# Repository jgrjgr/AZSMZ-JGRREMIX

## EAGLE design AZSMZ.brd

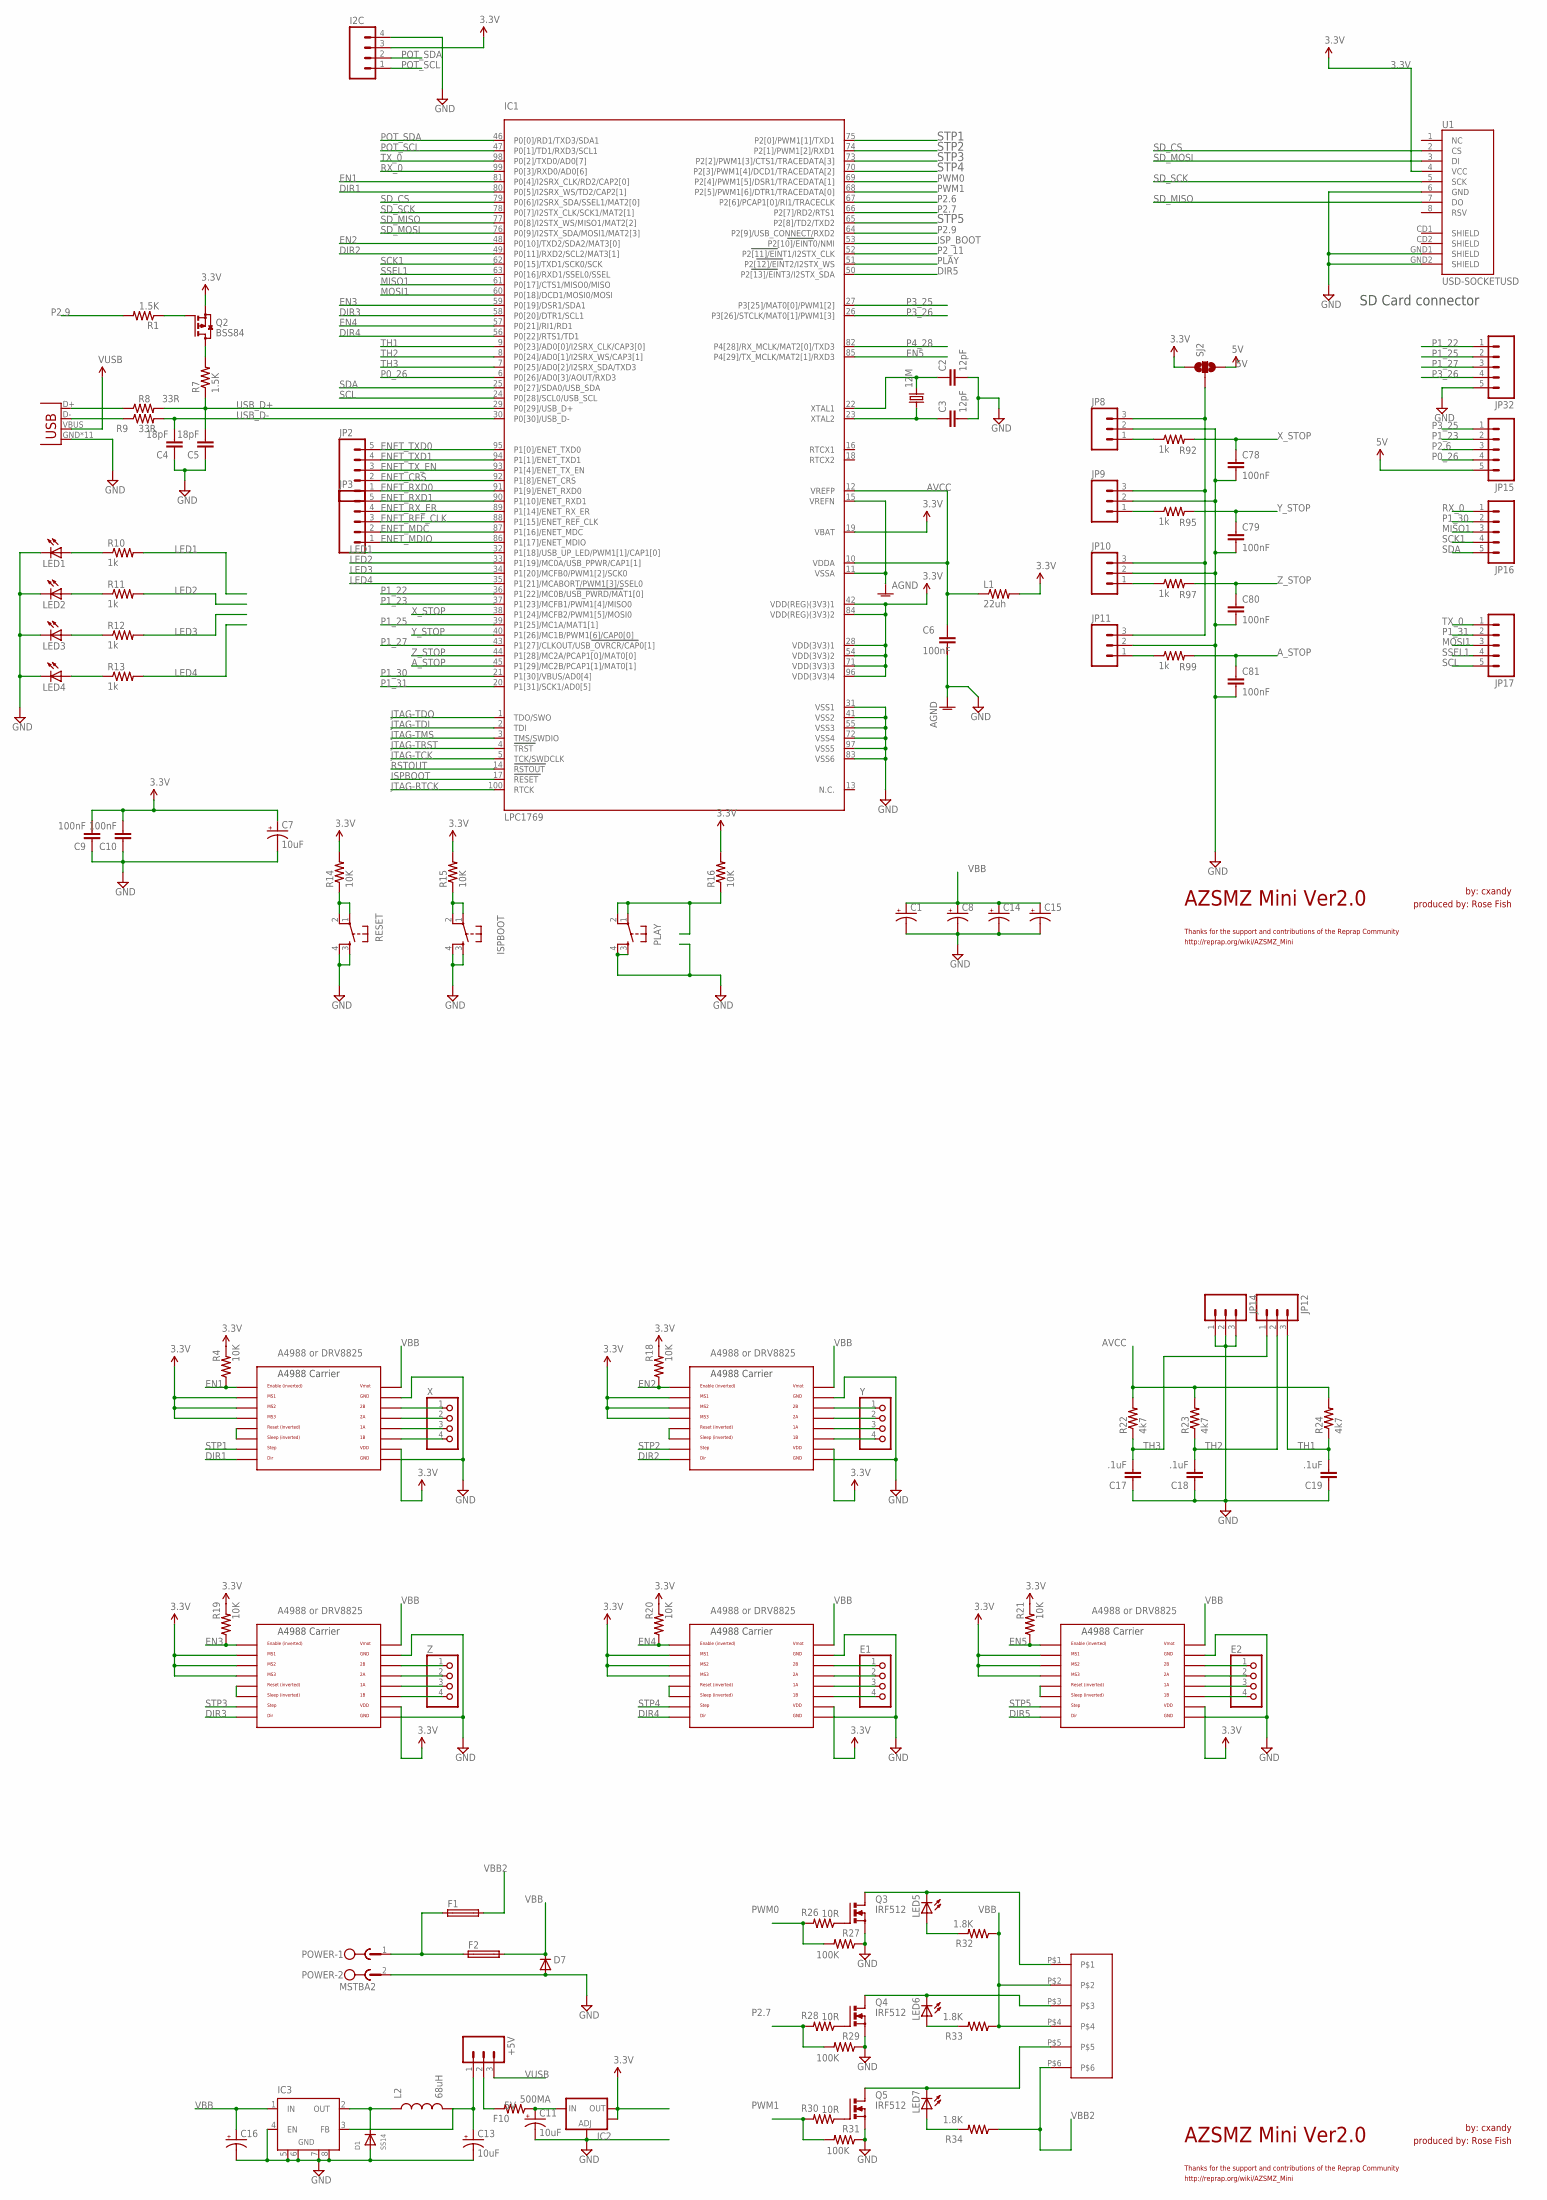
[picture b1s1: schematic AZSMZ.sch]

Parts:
12M: CRYSTALHC49S; HC49/S
+5V: M03PTH; 1X03
C1, C8, C14, C15, C16: CPOL-US153CLV-0605; 153CLV-0605
C2, C3: 12pF; C0805K
C4: 18pF; C0805K
C5: 18pF; C0805
C6, C9, C78, C79, C80, C81: 100nF; C0805K
C7, C11, C13: 10uF; EIA3216
C10: 100nF; C0805
C17, C18, C19: .1uF; C0805K
D1: SS14; SOD-123
D7: IN4004; SOD-123_MINI-SMA
E1, E2: PINHD-1X4; 1X04
F1: REPRAPJR_PTCFUSEMFR1100; REPRAPJR_MFR1100
F2: REPRAPJR_PTCFUSE; REPRAPJR_MFR500
F10: 500MA; R1206
I2C: M041.27MM; 1X04-1.27MM
IC1: LPC1769; LQFP100
IC2: V_REG_LM1117SOT223; SOT223
IC3: XL1509; SO08
ISP_BOOT: TAC_SWITCHSMD; TACTILE_SWITCH_SMD
JP2, JP3: M051.27MM; 1X05-1.27MM
JP8, JP9, JP10, JP11, JP12, JP14: M03PTH; 1X03
JP15, JP16, JP17, JP32: M05PTH; 1X05
L1: 22uh; M1206
L2: 68uH; CR54
LED1, LED2, LED3, LED4, LED5, LED6, LED7: LEDCHIP-LED0805; CHIP-LED0805
PLAY: TAC_SWITCHSMD; TACTILE_SWITCH_SMD
POWER: MSTBA2
Q2: BSS84; SOT23
Q3, Q4, Q5: IRF512; TO220BV
R1, R7: 1.5K; M0805
R4, R14, R15, R16, R18, R19, R20, R21: 10K; M0805
R8, R9: 33R; M0805
R10, R11, R12, R13, R92, R95, R97, R99: 1k; M0805
R22, R23, R24: 4k7; M0805
R26, R28, R30: 10R; M0805
R27, R29, R31: 100K; M0805
R32, R33, R34: 1.8K; M0805
RESET: TAC_SWITCHSMD; TACTILE_SWITCH_SMD
SJ2: SOLDERJUMPER_2WAYS; SJ_3
U1: USD-SOCKETUSD; USD-SOCKET-PP
U$3: 282837-6
U$11, U$12, U$13, U$14, U$15: A4988BREAKOUT
X: PINHD-1X4; 1X04
X1: USB-MICROB
Y: PINHD-1X4; 1X04
Z: PINHD-1X4; 1X04

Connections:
3.3V: C7.A (+), C9.2, C10.2, I2C.3, IC1.19 (VBAT), IC1.28 (VDD(3V3)1), IC1.42 (VDD(REG)(3V3)1), IC1.54 (VDD(3V3)2), IC1.71 (VDD(3V3)3), IC1.84 (VDD(REG)(3V3)2), IC1.96 (VDD(3V3)4), IC2.2 (OUT), IC2.4 (OUT), L1.2, Q2.2 (S), R4.2, R14.2, R15.2, R16.2, R18.2, R19.2, R20.2, R21.2, SJ2.1, U1.4 (VCC), U$11.MS1, U$11.MS2, U$11.MS3, U$11.VDD, U$12.MS1, U$12.MS2, U$12.MS3, U$12.VDD, U$13.MS1, U$13.MS2, U$13.MS3, U$13.VDD, U$14.MS1, U$14.MS2, U$14.MS3, U$14.VDD, U$15.MS1, U$15.MS2, U$15.MS3, U$15.VDD
5V: C11.A (+), F10.1, IC2.3 (IN), JP15.5, SJ2.3
AGND: C6.2, IC1.11 (VSSA), IC1.15 (VREFN)
AVCC: C6.1, IC1.10 (VDDA), IC1.12 (VREFP), L1.1, R22.2, R23.2, R24.2
A_STOP: C81.1, IC1.45 (P1[29]/MC2B/PCAP1[1]/MAT0[1]), R99.2
DIR1: IC1.80 (P0[5]/I2SRX_WS/TD2/CAP2[1]), U$11.DIR
DIR2: IC1.49 (P0[11]/RXD2/SCL2/MAT3[1]), U$12.DIR
DIR3: IC1.58 (P0[20]/DTR1/SCL1), U$13.DIR
DIR4: IC1.56 (P0[22]/RTS1/TD1), U$14.DIR
DIR5: IC1.50 (P2[13]/EINT3/I2STX_SDA), U$15.DIR
EN1: IC1.81 (P0[4]/I2SRX_CLK/RD2/CAP2[0]), R4.1, U$11.EN
EN2: IC1.48 (P0[10]/TXD2/SDA2/MAT3[0]), R18.1, U$12.EN
EN3: IC1.59 (P0[19]/DSR1/SDA1), R19.1, U$13.EN
EN4: IC1.57 (P0[21]/RI1/RD1), R20.1, U$14.EN
EN5: IC1.85 (P4[29]/TX_MCLK/MAT2[1]/RXD3), R21.1, U$15.EN
ENET_CRS: IC1.92 (P1[8]/ENET_CRS), JP2.2
ENET_MDC: IC1.87 (P1[16]/ENET_MDC), JP3.2
ENET_MDIO: IC1.86 (P1[17]/ENET_MDIO), JP3.1
ENET_REF_CLK: IC1.88 (P1[15]/ENET_REF_CLK), JP3.3
ENET_RXD0: IC1.91 (P1[9]/ENET_RXD0), JP2.1
ENET_RXD1: IC1.90 (P1[10]/ENET_RXD1), JP3.5
ENET_RX_ER: IC1.89 (P1[14]/ENET_RX_ER), JP3.4
ENET_TXD0: IC1.95 (P1[0]/ENET_TXD0), JP2.5
ENET_TXD1: IC1.94 (P1[1]/ENET_TXD1), JP2.4
ENET_TX_EN: IC1.93 (P1[4]/ENET_TX_EN), JP2.3
GND: C1.-, C2.2, C3.2, C4.1, C5.1, C7.C (-), C8.-, C9.1, C10.1, C11.C (-), C13.C (-), C14.-, C15.-, C16.-, C17.1, C18.1, C19.1, C78.2, C79.2, C80.2, C81.2, D1.A, D7.A, I2C.4, IC1.31 (VSS1), IC1.41 (VSS2), IC1.55 (VSS3), IC1.72 (VSS4), IC1.83 (VSS6), IC1.97 (VSS5), IC2.1 (ADJ), IC3.4 (EN), IC3.5 (GND), IC3.6 (GND1), IC3.7 (GND2), IC3.8 (GND), ISP_BOOT.3, ISP_BOOT.4, JP8.2, JP9.2, JP10.2, JP11.2, JP14.1, JP14.2, JP14.3, JP32.5, LED1.C, LED2.C, LED3.C, LED4.C, PLAY.3, PLAY.4, POWER.2, Q3.S, Q4.S, Q5.S, R27.1, R29.1, R31.1, RESET.3, RESET.4, U1.6 (GND), U1.GND1 (SHIELD), U1.GND2 (SHIELD), U$11.GND, U$11.GND@0 (GND), U$12.GND, U$12.GND@0 (GND), U$13.GND, U$13.GND@0 (GND), U$14.GND, U$14.GND@0 (GND), U$15.GND, U$15.GND@0 (GND), X1.GND, X1.MT1 (GND), X1.MT2 (GND), X1.MT3 (GND), X1.MT4 (GND), X1.P$1 (GND), X1.P$2 (GND), X1.P$3 (GND), X1.P$4 (GND), X1.P$5 (GND), X1.P$6 (GND)
ISPBOOT: IC1.17 (RESET), R14.1, RESET.1, RESET.2
ISP_BOOT: IC1.53 (P2[10]/EINT0/NMI), ISP_BOOT.1, ISP_BOOT.2, R15.1
JTAG-RTCK: IC1.100 (RTCK)
JTAG-TCK: IC1.5 (TCK/SWDCLK)
JTAG-TDI: IC1.2 (TDI)
JTAG-TDO: IC1.1 (TDO/SWO)
JTAG-TMS: IC1.3 (TMS/SWDIO)
JTAG-TRST: IC1.4 (TRST)
LED1: IC1.32 (P1[18]/USB_UP_LED/PWM1[1]/CAP1[0]), R10.2
LED2: IC1.33 (P1[19]/MC0A/USB_PPWR/CAP1[1]), R11.2
LED3: IC1.34 (P1[20]/MCFB0/PWM1[2]/SCK0), R12.2
LED4: IC1.35 (P1[21]/MCABORT/PWM1[3]/SSEL0), R13.2
MISO1: IC1.61 (P0[17]/CTS1/MISO0/MISO), JP16.3
MOSI1: IC1.60 (P0[18]/DCD1/MOSI0/MOSI), JP17.3
unnamed: 12M.2, C2.1, IC1.22 (XTAL1)
unnamed: 12M.1, C3.1, IC1.23 (XTAL2)
unnamed: U$11.2B, X.1
unnamed: U$12.RST, U$12.SLP (SLEEP)
unnamed: Q2.1 (G), R1.1
unnamed: U$11.2A, X.2
unnamed: U$11.1A, X.3
unnamed: U$12.2B, Y.1
unnamed: U$11.RST, U$11.SLP (SLEEP)
unnamed: U$12.2A, Y.2
unnamed: U$12.1A, Y.3
unnamed: U$12.1B, Y.4
unnamed: U$11.1B, X.4
unnamed: U$13.RST, U$13.SLP (SLEEP)
unnamed: U$13.2B, Z.1
unnamed: U$13.2A, Z.2
unnamed: LED7.A, R34.2
unnamed: F1.1, F1.3 (1), F2.1, F2.3 (1), POWER.1
unnamed: U$13.1A, Z.3
unnamed: U$13.1B, Z.4
unnamed: U$14.RST, U$14.SLP (SLEEP)
unnamed: E1.1, U$14.2B
unnamed: E1.2, U$14.2A
unnamed: E1.3, U$14.1A
unnamed: E1.4, U$14.1B
unnamed: U$15.RST, U$15.SLP (SLEEP)
unnamed: E2.1, U$15.2B
unnamed: E2.2, U$15.2A
unnamed: E2.3, U$15.1A
unnamed: E2.4, U$15.1B
unnamed: Q3.G, R26.1
unnamed: Q4.G, R28.1
unnamed: Q5.G, R30.1
unnamed: +5V.2, F10.2
unnamed: D1.C, IC3.2 (OUT), L2.P$1 (1)
unnamed: +5V.1, C13.A (+), IC3.3 (FB), L2.P$2 (2)
unnamed: LED5.C, Q3.D, U$3.P$1
unnamed: LED6.C, Q4.D, U$3.P$3
unnamed: LED7.C, Q5.D, U$3.P$5
unnamed: LED6.A, R33.2
unnamed: LED5.A, R32.2
unnamed: Q2.3 (D), R7.2
unnamed: R8.1, X1.D+
unnamed: R9.1, X1.D-
unnamed: LED4.A, R13.1
unnamed: LED3.A, R12.1
unnamed: LED2.A, R11.1
unnamed: LED1.A, R10.1
unnamed: JP9.1, R95.1
unnamed: JP8.3, JP9.3, JP10.3, JP11.3, SJ2.2
unnamed: JP10.1, R97.1
unnamed: JP11.1, R99.1
unnamed: JP8.1, R92.1
P0_26: IC1.6 (P0[26]/AD0[3]/AOUT/RXD3), JP15.4
P1_22: IC1.36 (P1[22]/MC0B/USB_PWRD/MAT1[0]), JP32.1
P1_23: IC1.37 (P1[23]/MCFB1/PWM1[4]/MISO0), JP15.2
P1_25: IC1.39 (P1[25]/MC1A/MAT1[1]), JP32.2
P1_27: IC1.43 (P1[27]/CLKOUT/USB_OVRCR/CAP0[1]), JP32.3
P1_30: IC1.21 (P1[30]/VBUS/AD0[4]), JP16.2
P1_31: IC1.20 (P1[31]/SCK1/AD0[5]), JP17.2
P2.6: IC1.67 (P2[6]/PCAP1[0]/RI1/TRACECLK), JP15.3
P2.7: IC1.66 (P2[7]/RD2/RTS1), R28.2, R29.2
P2.9: IC1.64 (P2[9]/USB_CONNECT/RXD2), R1.2
P2_11: IC1.52 (P2[11]/EINT1/I2STX_CLK)
P3_25: IC1.27 (P3[25]/MAT0[0]/PWM1[2]), JP15.1
P3_26: IC1.26 (P3[26]/STCLK/MAT0[1]/PWM1[3]), JP32.4
P4_28: IC1.82 (P4[28]/RX_MCLK/MAT2[0]/TXD3)
PLAY: IC1.51 (P2[12]/EINT2/I2STX_WS), PLAY.1, PLAY.2, R16.1
POT_SCL: I2C.1, IC1.47 (P0[1]/TD1/RXD3/SCL1)
POT_SDA: I2C.2, IC1.46 (P0[0]/RD1/TXD3/SDA1)
PWM0: IC1.69 (P2[4]/PWM1[5]/DSR1/TRACEDATA[1]), R26.2, R27.2
PWM1: IC1.68 (P2[5]/PWM1[6]/DTR1/TRACEDATA[0]), R30.2, R31.2
RSTOUT: IC1.14 (RSTOUT)
RX_0: IC1.99 (P0[3]/RXD0/AD0[6]), JP16.1
SCK1: IC1.62 (P0[15]/TXD1/SCK0/SCK), JP16.4
SCL: IC1.24 (P0[28]/SCL0/USB_SCL), JP17.5
SDA: IC1.25 (P0[27]/SDA0/USB_SDA), JP16.5
SD_CS: IC1.79 (P0[6]/I2SRX_SDA/SSEL1/MAT2[0]), U1.2 (CS)
SD_MISO: IC1.77 (P0[8]/I2STX_WS/MISO1/MAT2[2]), U1.7 (DO)
SD_MOSI: IC1.76 (P0[9]/I2STX_SDA/MOSI1/MAT2[3]), U1.3 (DI)
SD_SCK: IC1.78 (P0[7]/I2STX_CLK/SCK1/MAT2[1]), U1.5 (SCK)
SSEL1: IC1.63 (P0[16]/RXD1/SSEL0/SSEL), JP17.4
STP1: IC1.75 (P2[0]/PWM1[1]/TXD1), U$11.STEP
STP2: IC1.74 (P2[1]/PWM1[2]/RXD1), U$12.STEP
STP3: IC1.73 (P2[2]/PWM1[3]/CTS1/TRACEDATA[3]), U$13.STEP
STP4: IC1.70 (P2[3]/PWM1[4]/DCD1/TRACEDATA[2]), U$14.STEP
STP5: IC1.65 (P2[8]/TD2/TXD2), U$15.STEP
TH1: C19.2, IC1.9 (P0[23]/AD0[0]/I2SRX_CLK/CAP3[0]), JP12.3, R24.1
TH2: C18.2, IC1.8 (P0[24]/AD0[1]/I2SRX_WS/CAP3[1]), JP12.2, R23.1
TH3: C17.2, IC1.7 (P0[25]/AD0[2]/I2SRX_SDA/TXD3), JP12.1, R22.1
TX_0: IC1.98 (P0[2]/TXD0/AD0[7]), JP17.1
USB_D+: C5.2, IC1.29 (P0[29]/USB_D+), R7.1, R8.2
USB_D-: C4.2, IC1.30 (P0[30]/USB_D-), R9.2
VBB: C1.+, C8.+, C14.+, C15.+, C16.+, D7.C, F2.2, IC3.1 (IN), R32.1, R33.1, U$3.P$2, U$3.P$4, U$11.VMOT, U$12.VMOT, U$13.VMOT, U$14.VMOT, U$15.VMOT
VBB2: F1.2, R34.1, U$3.P$6
VUSB: +5V.3, X1.VBUS
X_STOP: C78.1, IC1.38 (P1[24]/MCFB2/PWM1[5]/MOSI0), R92.2
Y_STOP: C79.1, IC1.40 (P1[26]/MC1B/PWM1[6]/CAP0[0]), R95.2
Z_STOP: C80.1, IC1.44 (P1[28]/MC2A/PCAP1[0]/MAT0[0]), R97.2

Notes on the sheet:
SD Card connector
AZSMZ Mini Ver2.0
by: cxandy
produced by: Rose Fish
http://reprap.org/wiki/AZSMZ_Mini
Thanks for the support and contributions of the Reprap Community
A4988 or DRV8825

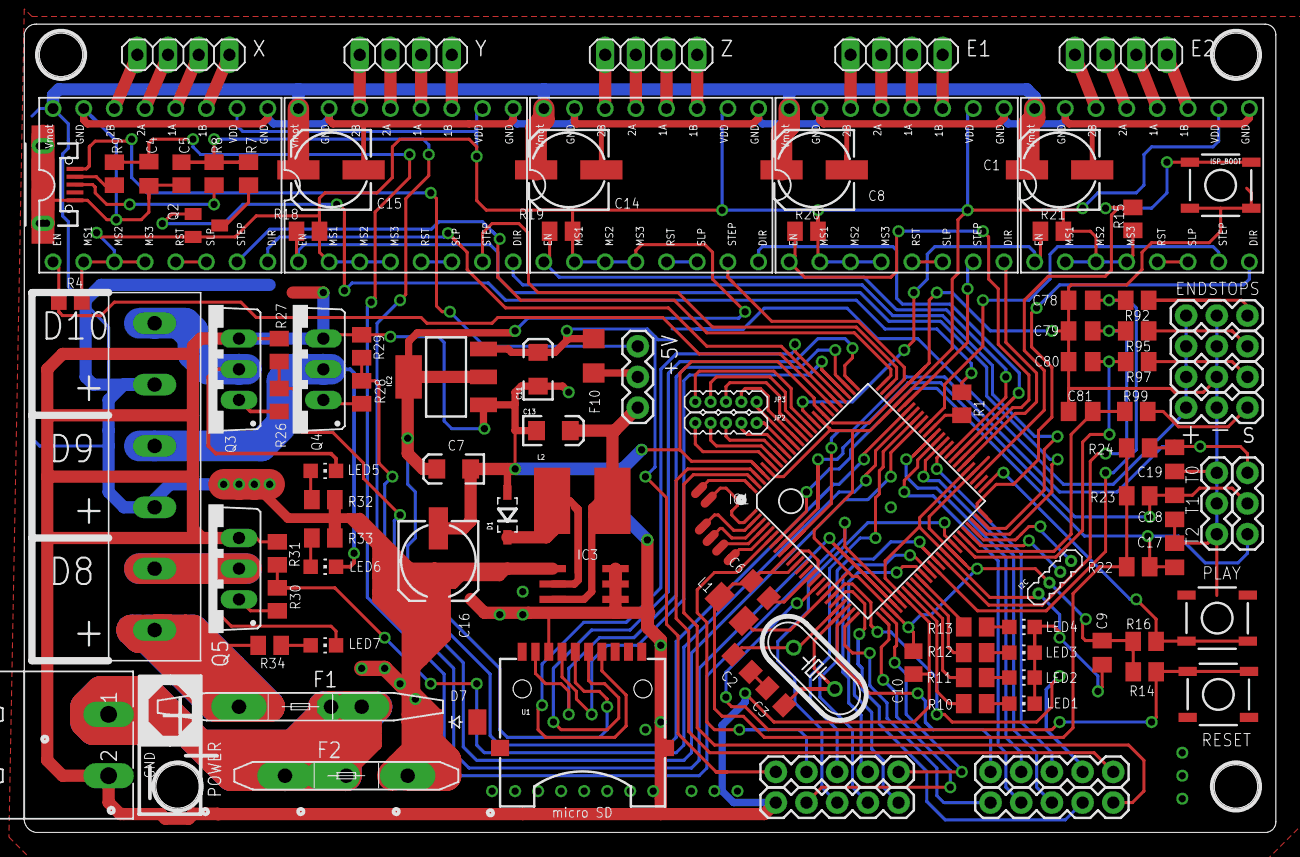
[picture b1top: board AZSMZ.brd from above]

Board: 4 copper layers, 103.6 x 66.9 mm, 108 parts (1 on the bottom side), 130 nets.

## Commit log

2015-08-04 initial upload
